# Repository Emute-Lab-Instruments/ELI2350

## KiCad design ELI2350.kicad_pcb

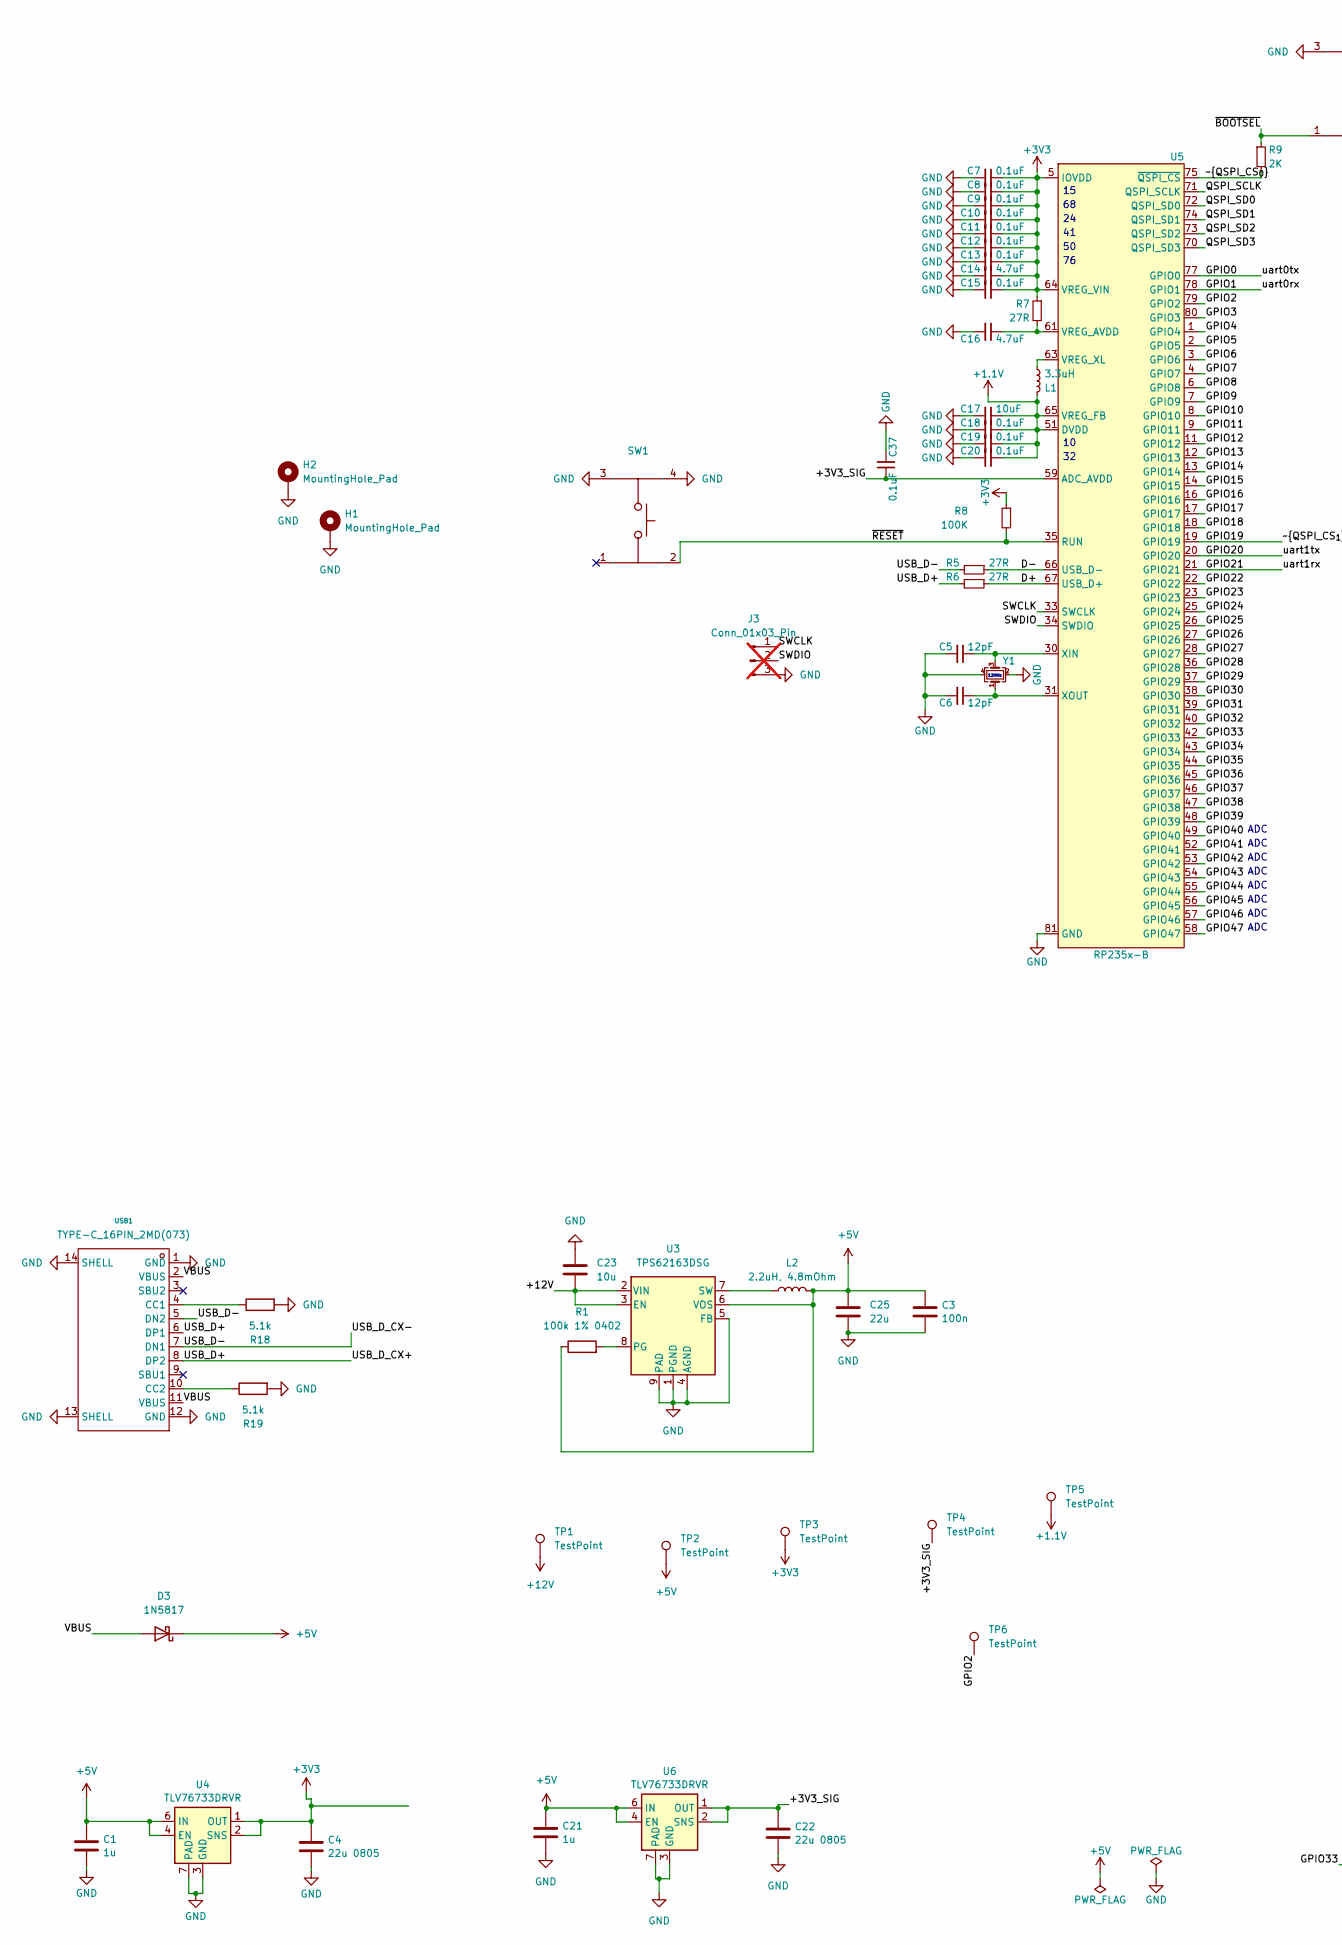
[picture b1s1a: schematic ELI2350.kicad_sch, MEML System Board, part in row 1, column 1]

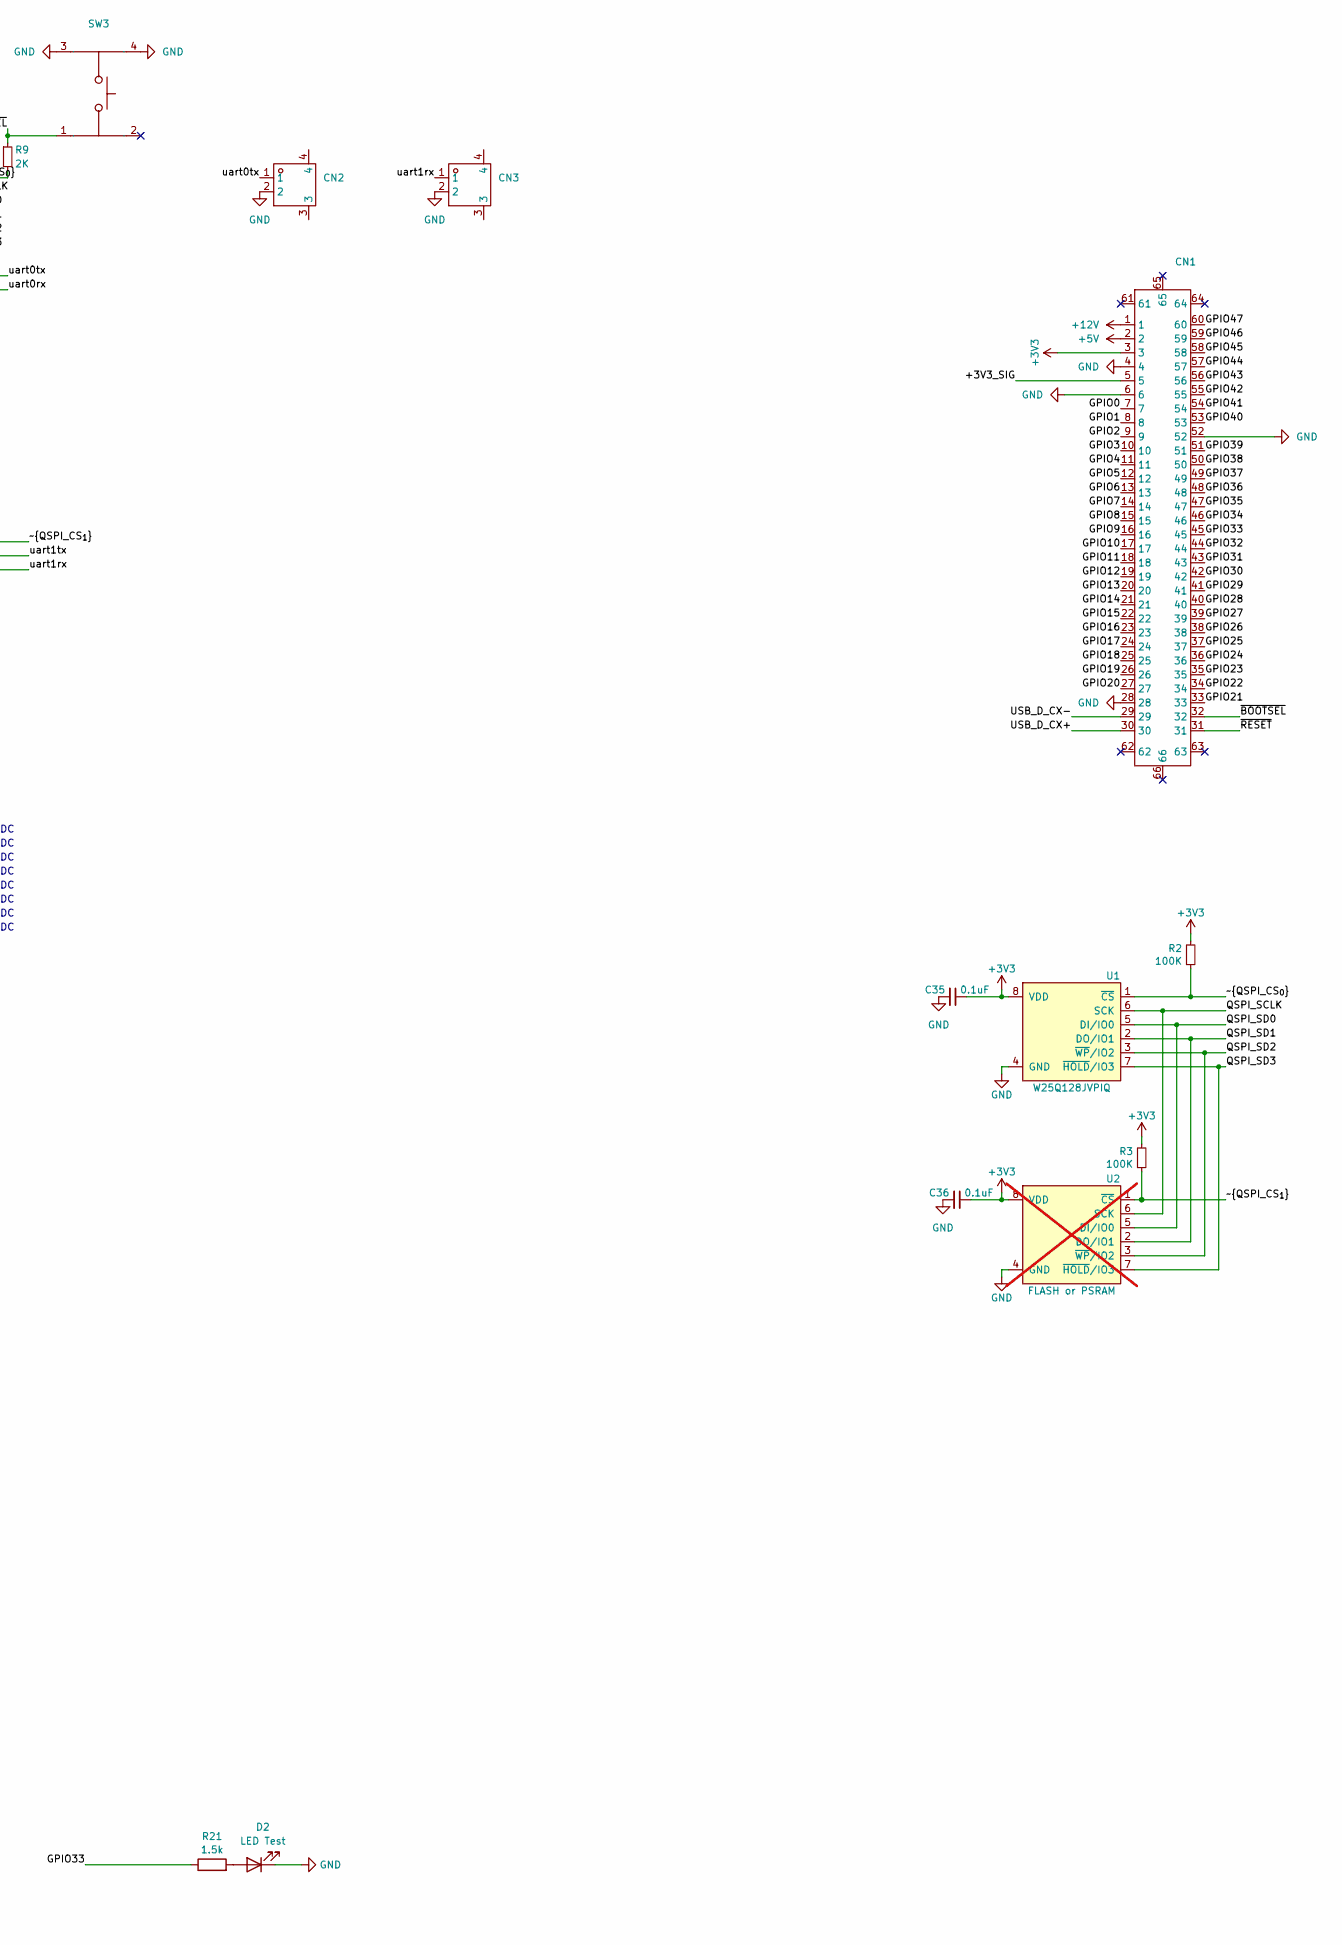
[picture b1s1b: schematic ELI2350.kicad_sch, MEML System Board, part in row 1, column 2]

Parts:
C1, C21: 1u; C_0603_1608Metric_Pad1.08x0.95mm_HandSolder
C3: 100n; C_0603_1608Metric
C4, C22: 22u 0805; C_0805_2012Metric_Pad1.18x1.45mm_HandSolder
C5, C6: 12pF; C_0603_1608Metric
C7, C8, C9, C10, C11, C12, C13, C15, C18, C19, C20, C35, C36, C37: 0.1uF; C_0603_1608Metric
C14, C16: 4.7uF; C_0603_1608Metric
C17: 10uF; C_0603_1608Metric
C23: 10u; C_0805_2012Metric
C25: 22u; C_0805_2012Metric
CN1: CONN-SMD_60P-P0.50_HCTL_HC-PBB23L-60DS-0.5V-G2-01; Manufacturer Part HC-PBB23L-60DS-0.5V-G2-01; JLC C22390096
CN2, CN3: CONN-SMD_2P-P1.50_XUNPU_WAFER-ZH1.5-2PWB; Manufacturer Part WAFER-ZH1.5-2PWB; JLC C3029422
D2: LED Test; LED_0805_2012Metric
D3: 1N5817; D_SOD-323
H1, H2: MountingHole_Pad; MountingHole_2.2mm_M2_Pad
J3: Conn_01x03_Pin; PinHeader_1x03_P2.54mm_Vertical_SMD_Pin1Left; not fitted
L1: 3.3uH; IND-SMD_L2.0-W1.6_AOTA-B201610S3R3-101-T; JLC C42411119
L2: 2.2uH, 4.8mOhm; L_Sunlord_SWPA4020S
R1: 100k 1% 0402; R_0402_1005Metric
R2, R3, R8: 100K; R_0603_1608Metric
R5, R6, R7: 27R; R_0603_1608Metric
R9: 2K; R_0603_1608Metric
R18, R19: 5.1k; R_0402_1005Metric
R21: 1.5k; R_0603_1608Metric
SW1, SW3: SW-SMD_4P-L3.5-W2.9-P1.30-LS4.8; Manufacturer Part SKSCLAE010; JLC C130445
TP1, TP2, TP3, TP4, TP5, TP6: TestPoint; TestPoint_Pad_1.5x1.5mm
U1: W25Q128JVPIQ; WSON-8-1EP_6x5mm_P1.27mm_EP3.4x4mm; JLC C190862
U2: FLASH or PSRAM; SSOP-8_5.25x5.24mm_P1.27mm; not fitted
U3: TPS62163DSG; WSON-8-1EP_2x2mm_P0.5mm_EP0.9x1.6mm_ThermalVias; JLC C97534
U4, U6: TLV76733DRVR; WSON-6-1EP_2x2mm_P0.65mm_EP1x1.6mm_ThermalVias; JLC C2848334
U5: RP235x-B; QFN-80_EP_10x10_Pitch0.4mm; JLC C42415655
USB1: TYPE-C_16PIN_2MD(073); USB-C-SMD_TYPE-C-6PIN-2MD-073; JLC C2765186
Y1: CM4012M00012001; Crystal_SMD_2520-4Pin_2.5x2.0mm; LCSC C7294610

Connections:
+1.1V: C17.1, C18.1, C19.1, C20.1, L1.2, TP5.1, U5.10 (DVDD), U5.32 (DVDD), U5.51 (DVDD), U5.65 (VREG_FB)
+3V3: C4.1, C7.1, C8.1, C9.1, C10.1, C11.1, C12.1, C13.1, C14.1, C15.1, C35.1, C36.1, CN1.3, R2.2, R3.2, R7.1, R8.1, TP3.1, U1.8 (VDD), U2.8 (VDD), U4.1 (OUT), U4.2 (SNS), U5.5 (IOVDD), U5.15 (IOVDD), U5.24 (IOVDD), U5.29 (IOVDD), U5.41 (IOVDD), U5.50 (IOVDD), U5.60 (IOVDD), U5.64 (VREG_VIN), U5.68 (IOVDD), U5.69 (IOVDD), U5.76 (IOVDD)
+5V: C1.1, C3.1, C21.1, C25.1, CN1.2, D3.1 (K), L2.2, R1.1, TP2.1, U3.6 (VOS), U4.4 (EN), U4.6 (IN), U6.4 (EN), U6.6 (IN)
+12V: C23.2, CN1.1, TP1.1, U3.2 (VIN), U3.3 (EN)
/+3V3_SIG: C22.1, C37.1, CN1.5, TP4.1, U5.59 (ADC_AVDD), U6.1 (OUT), U6.2 (SNS)
/D+: R6.1, U5.67 (USB_D+)
/D-: R5.1, U5.66 (USB_D-)
/GPIO0: CN1.7, CN2.1, U5.77 (GPIO0)
/GPIO1: CN1.8, U5.78 (GPIO1)
/GPIO2: CN1.9, TP6.1, U5.79 (GPIO2)
/GPIO3: CN1.10, U5.80 (GPIO3)
/GPIO4: CN1.11, U5.1 (GPIO4)
/GPIO5: CN1.12, U5.2 (GPIO5)
/GPIO6: CN1.13, U5.3 (GPIO6)
/GPIO7: CN1.14, U5.4 (GPIO7)
/GPIO8: CN1.15, U5.6 (GPIO8)
/GPIO9: CN1.16, U5.7 (GPIO9)
/GPIO10: CN1.17, U5.8 (GPIO10)
/GPIO11: CN1.18, U5.9 (GPIO11)
/GPIO12: CN1.19, U5.11 (GPIO12)
/GPIO13: CN1.20, U5.12 (GPIO13)
/GPIO14: CN1.21, U5.13 (GPIO14)
/GPIO15: CN1.22, U5.14 (GPIO15)
/GPIO16: CN1.23, U5.16 (GPIO16)
/GPIO17: CN1.24, U5.17 (GPIO17)
/GPIO18: CN1.25, U5.18 (GPIO18)
/GPIO19: CN1.26, R3.1, U2.1 (~CS), U5.19 (GPIO19)
/GPIO20: CN1.27, U5.20 (GPIO20)
/GPIO21: CN1.33, CN3.1, U5.21 (GPIO21)
/GPIO22: CN1.34, U5.22 (GPIO22)
/GPIO23: CN1.35, U5.23 (GPIO23)
/GPIO24: CN1.36, U5.25 (GPIO24)
/GPIO25: CN1.37, U5.26 (GPIO25)
/GPIO26: CN1.38, U5.27 (GPIO26)
/GPIO27: CN1.39, U5.28 (GPIO27)
/GPIO28: CN1.40, U5.36 (GPIO28)
/GPIO29: CN1.41, U5.37 (GPIO29)
/GPIO30: CN1.42, U5.38 (GPIO30)
/GPIO31: CN1.43, U5.39 (GPIO31)
/GPIO32: CN1.44, U5.40 (GPIO32)
/GPIO33: CN1.45, R21.1, U5.42 (GPIO33)
/GPIO34: CN1.46, U5.43 (GPIO34)
/GPIO35: CN1.47, U5.44 (GPIO35)
/GPIO36: CN1.48, U5.45 (GPIO36)
/GPIO37: CN1.49, U5.46 (GPIO37)
/GPIO38: CN1.50, U5.47 (GPIO38)
/GPIO39: CN1.51, U5.48 (GPIO39)
/GPIO40: CN1.53, U5.49 (GPIO40)
/GPIO41: CN1.54, U5.52 (GPIO41)
/GPIO42: CN1.55, U5.53 (GPIO42)
/GPIO43: CN1.56, U5.54 (GPIO43)
/GPIO44: CN1.57, U5.55 (GPIO44)
/GPIO45: CN1.58, U5.56 (GPIO45)
/GPIO46: CN1.59, U5.57 (GPIO46)
/GPIO47: CN1.60, U5.58 (GPIO47)
/QSPI_SCLK: U1.6 (SCK), U2.6 (SCK), U5.71 (QSPI_SCLK)
/QSPI_SD0: U1.5 (DI/IO0), U2.5 (DI/IO0), U5.72 (QSPI_SD0)
/QSPI_SD1: U1.2 (DO/IO1), U2.2 (DO/IO1), U5.74 (QSPI_SD1)
/QSPI_SD2: U1.3 (~WP/IO2), U2.3 (~WP/IO2), U5.73 (QSPI_SD2)
/QSPI_SD3: U1.7 (~HOLD/IO3), U2.7 (~HOLD/IO3), U5.70 (QSPI_SD3)
/SWCLK: J3.1, U5.33 (SWCLK)
/SWDIO: J3.2, U5.34 (SWDIO)
/USB_D+: CN1.30, R6.2, USB1.6 (DP1), USB1.8 (DP2)
/USB_D-: CN1.29, R5.2, USB1.5 (DN2), USB1.7 (DN1)
/VBUS: D3.2 (A), USB1.2 (VBUS), USB1.11 (VBUS)
/~BOOTSEL: CN1.32, R9.1, SW3.1
/~QSPI_CS_{0}: R2.1, R9.2, U1.1 (~CS), U5.75 (~QSPI_CS)
/~RESET: CN1.31, R8.2, SW1.2, U5.35 (RUN)
GND: C1.2, C3.2, C4.2, C5.2, C6.2, C7.2, C8.2, C9.2, C10.2, C11.2, C12.2, C13.2, C14.2, C15.2, C16.2, C17.2, C18.2, C19.2, C20.2, C21.2, C22.2, C23.1, C25.2, C35.2, C36.2, C37.2, CN1.4, CN1.6, CN1.28, CN1.52, CN2.2, CN3.2, D2.1 (K), H1.1, H2.1, J3.3, R18.2, R19.2, SW1.3, SW1.4, SW3.3, SW3.4, U1.4 (GND), U1.9 (GND), U2.4 (GND), U3.1 (PGND), U3.4 (AGND), U3.5 (FB), U3.9 (PAD), U4.3 (GND), U4.5 (GND), U4.7 (PAD), U5.62 (GND), U5.81 (GND), U6.3 (GND), U6.5 (GND), U6.7 (PAD), USB1.1 (GND), USB1.12 (GND), USB1.13 (SHELL), USB1.14 (SHELL), Y1.2, Y1.4
unnamed: D2.2 (A), R21.2
unnamed: R1.2, U3.8 (PG)
unnamed: L2.1, U3.7 (SW)
unnamed: C16.1, R7.2, U5.61 (VREG_AVDD)
unnamed: L1.1, U5.63 (VREG_XL)
unnamed: C5.1, U5.30 (XIN), Y1.3
unnamed: C6.1, U5.31 (XOUT), Y1.1
unnamed: R18.1, USB1.4 (CC1)
unnamed: R19.1, USB1.10 (CC2)

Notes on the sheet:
ADC
12MHz

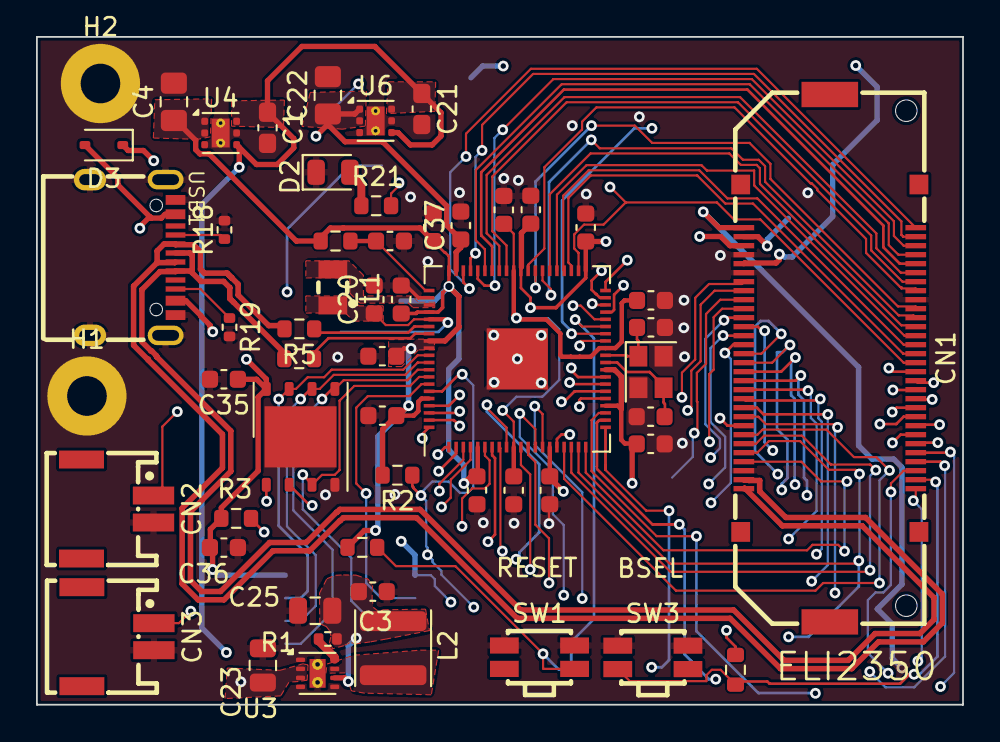
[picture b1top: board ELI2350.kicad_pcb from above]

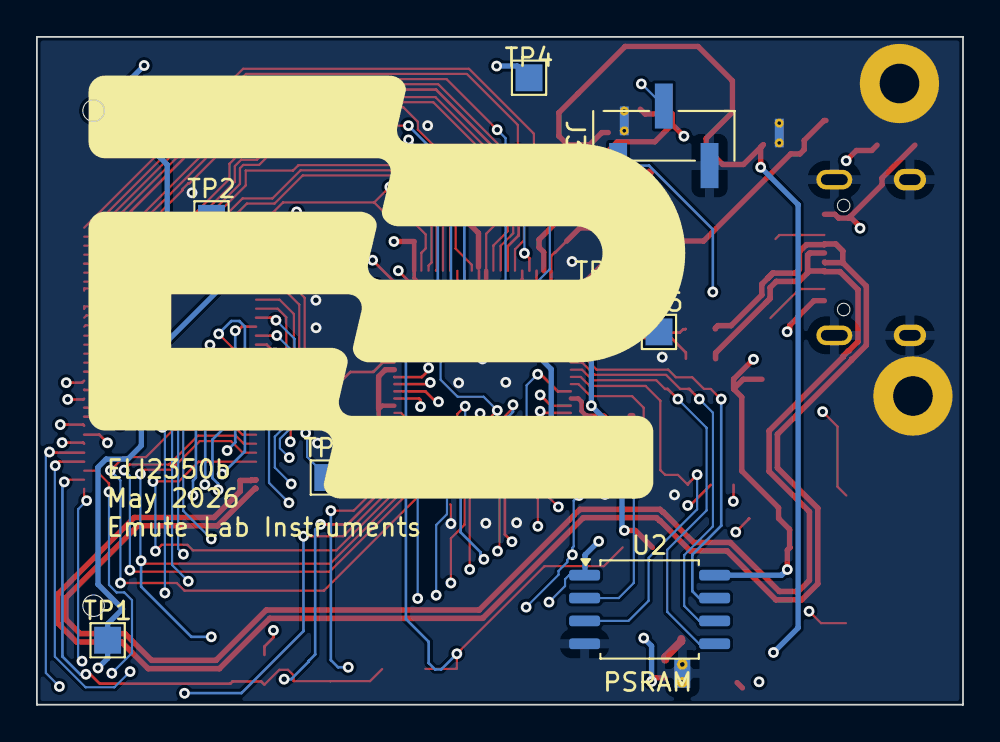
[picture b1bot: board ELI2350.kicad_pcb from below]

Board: 4 copper layers, 51.4 x 37.1 mm, 63 parts (8 on the bottom side), 78 nets.

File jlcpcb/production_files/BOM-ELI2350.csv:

Comment,Designator,Footprint,LCSC,Quantity
~,"SW1,SW3",SW-SMD_4P-L3.5-W2.9-P1.30-LS4.8,C130445,2
0.1uF,"C10,C11,C12,C13,C15,C18,C19,C20,C3,C35,C36,C37,C7,C8,C9",C_0603_1608Metric,C14663,15
1u,"C1,C21",C_0603_1608Metric_Pad1.08x0.95mm_HandSolder,C15849,2
W25Q128JVPIQ,U1,WSON-8-1EP_6x5mm_P1.27mm_EP3.4x4mm,C190862,1
4.7uF,"C14,C16",C_0603_1608Metric,C19666,2
~,CN1,CONN-SMD_60P-P0.50_HCTL_HC-PBB23L-60DS-0.5V-G2-01,C22390096,1
1.5k,R21,R_0603_1608Metric,C22843,1
2K,R9,R_0603_1608Metric,C22975,1
27R,"R5,R6,R7",R_0603_1608Metric,C25224,3
100k 1% 0402,R1,R_0402_1005Metric,C25741,1
100K,"R2,R3,R8",R_0603_1608Metric,C25803,3
5.1k,"R18,R19",R_0402_1005Metric,C25905,2
TYPE-C_16PIN_2MD(073),USB1,USB-C-SMD_TYPE-C-6PIN-2MD-073,C2765186,1
TLV76733DRVR,"U4,U6",WSON-6-1EP_2x2mm_P0.65mm_EP1x1.6mm_ThermalVias,C2848334,2
~,"CN2,CN3",CONN-SMD_2P-P1.50_XUNPU_WAFER-ZH1.5-2PWB,C3029422,2
12pF,"C5,C6",C_0603_1608Metric,C38523,2
3.3uH,L1,IND-SMD_L2.0-W1.6_AOTA-B201610S3R3-101-T,C42411119,1
RP235x-B,U5,QFN-80_EP_10x10_Pitch0.4mm,C42415655,1
10u,C23,C_0805_2012Metric,C440198,1
22u 0805,"C22,C25,C4",C_0805_2012Metric_Pad1.18x1.45mm_HandSolder,C45783,3
1N5817,D3,D_SOD-323,C5190152,1
CM4012M00012001,Y1,Crystal_SMD_2520-4Pin_2.5x2.0mm,C7294610,1
LED Test,D2,LED_0805_2012Metric,C7496841,1
10uF,C17,C_0603_1608Metric,C96446,1
TPS62163DSG,U3,WSON-8-1EP_2x2mm_P0.5mm_EP0.9x1.6mm_ThermalVias,C97534,1
"2.2uH, 4.8mOhm",L2,L_Sunlord_SWPA4020S,C98361,1

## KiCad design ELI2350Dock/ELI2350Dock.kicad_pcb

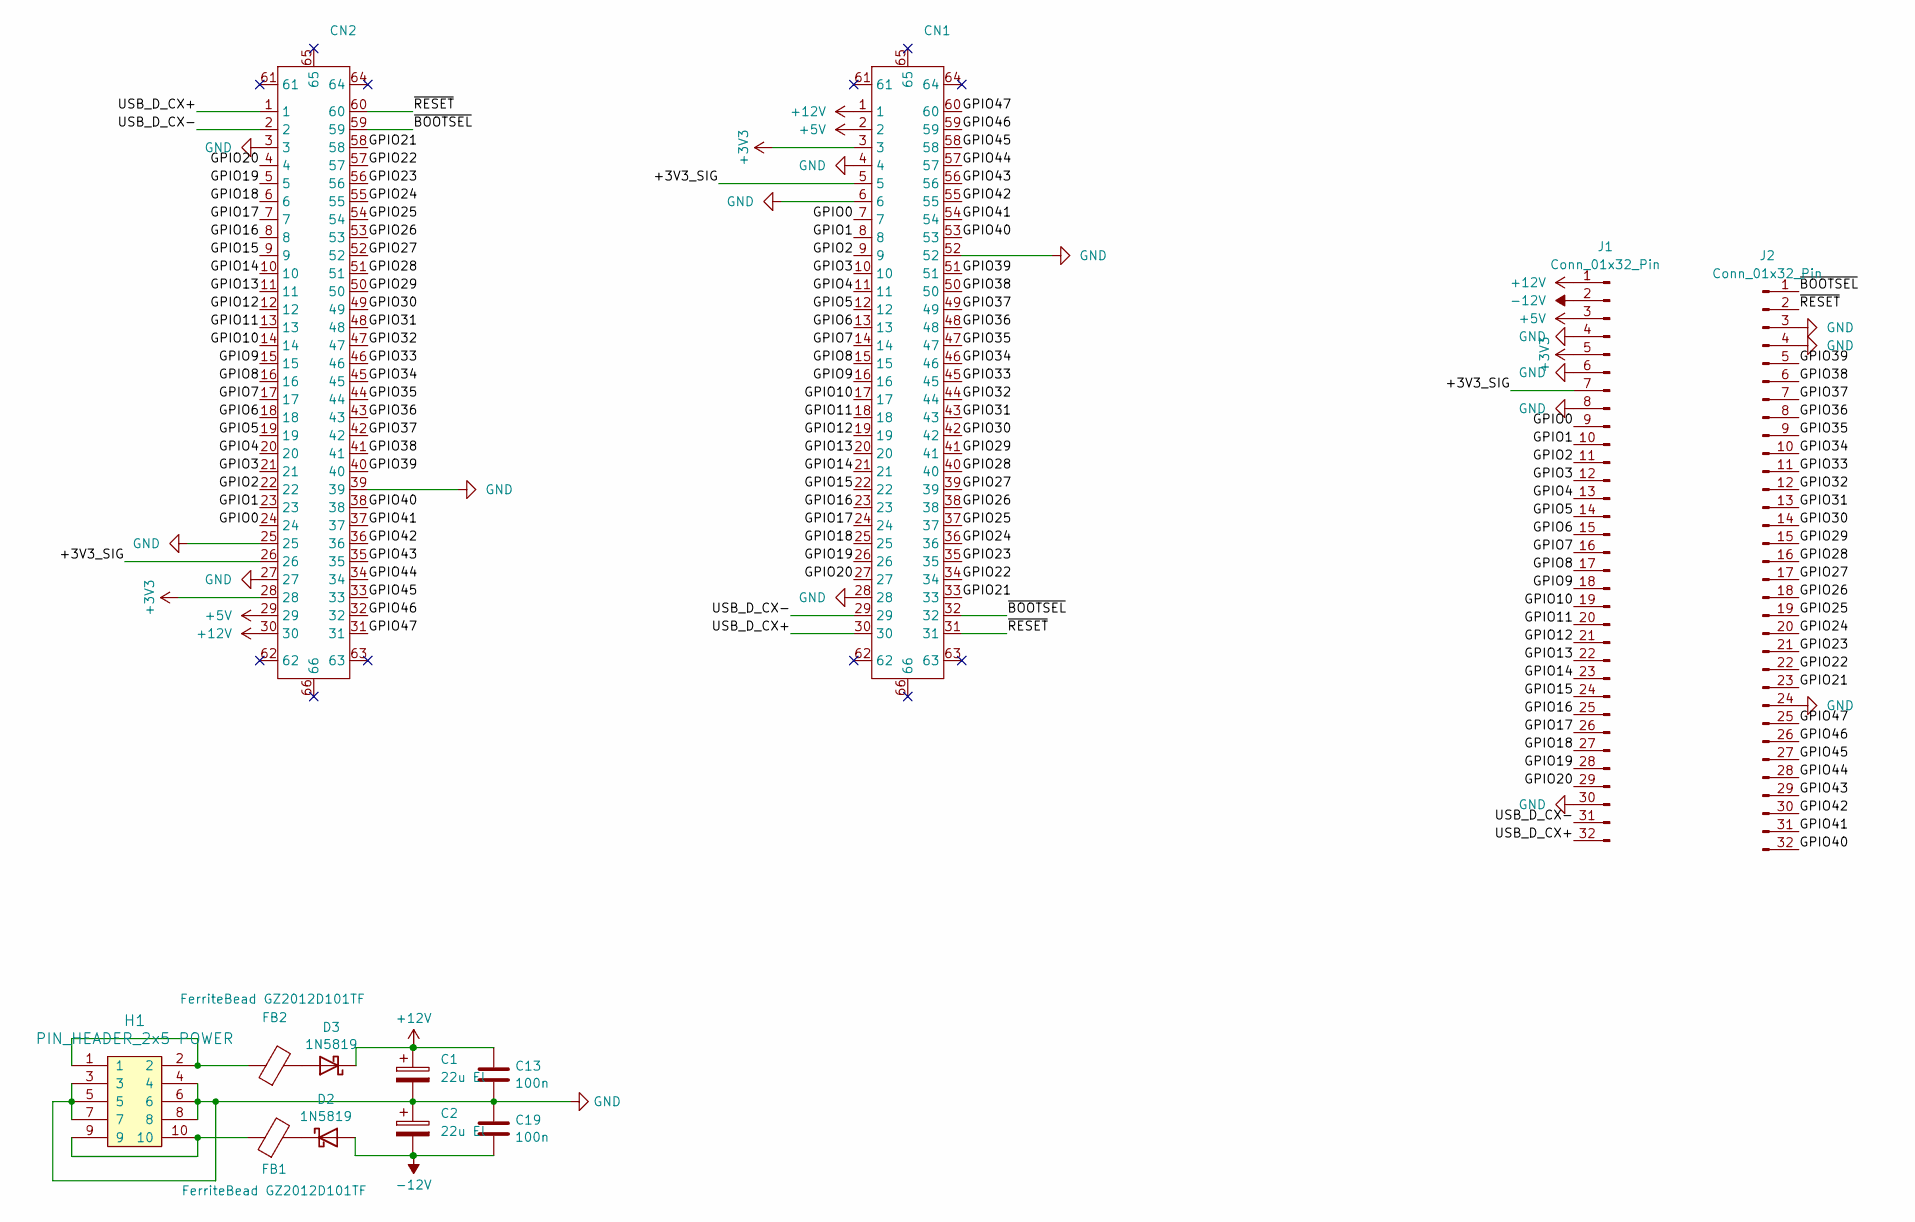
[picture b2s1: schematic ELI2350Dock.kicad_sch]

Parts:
C1, C2: 22u El; CP_Elec_4x3.9; JLC C250865
C13, C19: 100n; C_0603_1608Metric; JLC C14663
CN1: CONN-SMD_60P-P0.50_HCTL_HC-PBB23L-60DS-0.5V-G2-01; Manufacturer Part HC-PBB23L-60DS-0.5V-G2-01; JLC C22390096
CN2: CONN-SMD_HC-PBB23L-60DP-0.5V10-G2-01; Manufacturer Part HC-PBB23L-60DS-0.5V-G2-01; JLC C22390101
D2: 1N5819; D_SOD-323; JLC C191023
D3: 1N5819; D_SOD-323
FB1, FB2: FerriteBead GZ2012D101TF; R_0805_2012Metric; JLC C1017
H1: PIN_HEADER_2x5 POWER; PinHeader_2x05_P2.54mm_Vertical_SMD; JLC C3294463
J1, J2: Conn_01x32_Pin; PinSocket_1x32_P2.54mm_Vertical

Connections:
+3V3: CN1.3, CN2.28, J1.5
+5V: CN1.2, CN2.29, J1.3
+12V: C1.1, C13.1, CN1.1, CN2.30, D3.1 (K), J1.1
-12V: C2.2, C19.2, D2.2 (A), J1.2
/+3V3_SIG: CN1.5, CN2.26, J1.7
/GPIO0: CN1.7, CN2.24, J1.9
/GPIO1: CN1.8, CN2.23, J1.10
/GPIO2: CN1.9, CN2.22, J1.11
/GPIO3: CN1.10, CN2.21, J1.12
/GPIO4: CN1.11, CN2.20, J1.13
/GPIO5: CN1.12, CN2.19, J1.14
/GPIO6: CN1.13, CN2.18, J1.15
/GPIO7: CN1.14, CN2.17, J1.16
/GPIO8: CN1.15, CN2.16, J1.17
/GPIO9: CN1.16, CN2.15, J1.18
/GPIO10: CN1.17, CN2.14, J1.19
/GPIO11: CN1.18, CN2.13, J1.20
/GPIO12: CN1.19, CN2.12, J1.21
/GPIO13: CN1.20, CN2.11, J1.22
/GPIO14: CN1.21, CN2.10, J1.23
/GPIO15: CN1.22, CN2.9, J1.24
/GPIO16: CN1.23, CN2.8, J1.25
/GPIO17: CN1.24, CN2.7, J1.26
/GPIO18: CN1.25, CN2.6, J1.27
/GPIO19: CN1.26, CN2.5, J1.28
/GPIO20: CN1.27, CN2.4, J1.29
/GPIO21: CN1.33, CN2.58, J2.23
/GPIO22: CN1.34, CN2.57, J2.22
/GPIO23: CN1.35, CN2.56, J2.21
/GPIO24: CN1.36, CN2.55, J2.20
/GPIO25: CN1.37, CN2.54, J2.19
/GPIO26: CN1.38, CN2.53, J2.18
/GPIO27: CN1.39, CN2.52, J2.17
/GPIO28: CN1.40, CN2.51, J2.16
/GPIO29: CN1.41, CN2.50, J2.15
/GPIO30: CN1.42, CN2.49, J2.14
/GPIO31: CN1.43, CN2.48, J2.13
/GPIO32: CN1.44, CN2.47, J2.12
/GPIO33: CN1.45, CN2.46, J2.11
/GPIO34: CN1.46, CN2.45, J2.10
/GPIO35: CN1.47, CN2.44, J2.9
/GPIO36: CN1.48, CN2.43, J2.8
/GPIO37: CN1.49, CN2.42, J2.7
/GPIO38: CN1.50, CN2.41, J2.6
/GPIO39: CN1.51, CN2.40, J2.5
/GPIO40: CN1.53, CN2.38, J2.32
/GPIO41: CN1.54, CN2.37, J2.31
/GPIO42: CN1.55, CN2.36, J2.30
/GPIO43: CN1.56, CN2.35, J2.29
/GPIO44: CN1.57, CN2.34, J2.28
/GPIO45: CN1.58, CN2.33, J2.27
/GPIO46: CN1.59, CN2.32, J2.26
/GPIO47: CN1.60, CN2.31, J2.25
/USB_D_CX+: CN1.30, CN2.1, J1.32
/USB_D_CX-: CN1.29, CN2.2, J1.31
/~BOOTSEL: CN1.32, CN2.59, J2.1
/~RESET: CN1.31, CN2.60, J2.2
GND: C1.2, C2.1, C13.2, C19.1, CN1.4, CN1.6, CN1.28, CN1.52, CN2.3, CN2.25, CN2.27, CN2.39, H1.3, H1.4, H1.5, H1.6, H1.7, H1.8, J1.4, J1.6, J1.8, J1.30, J2.3, J2.4, J2.24
unnamed: D2.1 (K), FB1.2
unnamed: D3.2 (A), FB2.2
unnamed: FB1.1, H1.9, H1.10
unnamed: FB2.1, H1.1, H1.2

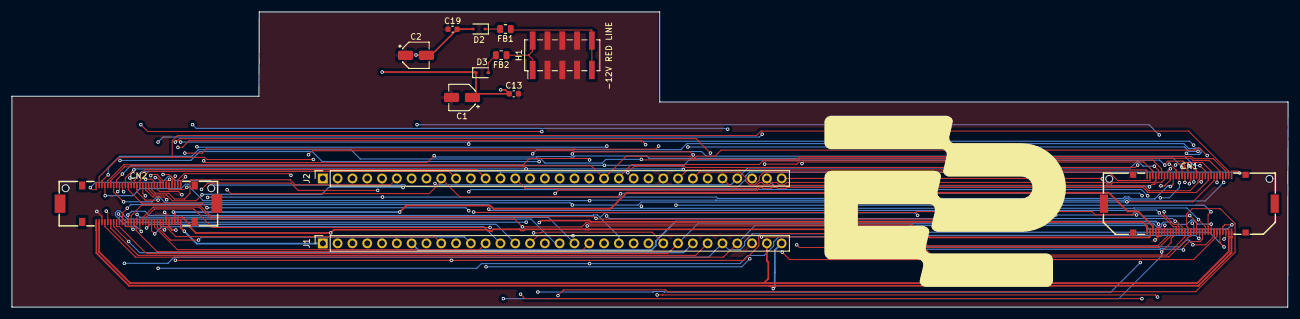
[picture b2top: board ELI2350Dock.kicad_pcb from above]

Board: 4 copper layers, 219.0 x 50.7 mm, 13 parts (0 on the bottom side), 62 nets.

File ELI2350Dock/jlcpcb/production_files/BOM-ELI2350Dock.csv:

Comment,Designator,Footprint,LCSC,Quantity
FerriteBead GZ2012D101TF,"FB1,FB2",R_0805_2012Metric,C1017,2
100n,"C13,C19",C_0603_1608Metric,C14663,2
1N5819,"D2,D3",D_SOD-323,C191023,2
~,CN1,CONN-SMD_60P-P0.50_HCTL_HC-PBB23L-60DS-0.5V-G2-01,C22390096,1
~,CN2,CONN-SMD_HC-PBB23L-60DP-0.5V10-G2-01,C22390101,1
22u El,"C1,C2",CP_Elec_4x3.9,C250865,2
PIN_HEADER_2x5 POWER,H1,PinHeader_2x05_P2.54mm_Vertical_SMD,C3294463,1
Conn_01x32_Pin,J1,PinSocket_1x32_P2.54mm_Vertical,,1
Conn_01x32_Pin,J2,PinSocket_1x32_P2.54mm_Vertical,,1

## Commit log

2025-11-03 innit
2025-11-07 alpha
2025-11-12 dock and near finished compute board
2025-11-17 doc pre-reroute
2026-05-14 bboard
